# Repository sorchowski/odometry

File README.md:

# Odometry

A collection of classes, Arduino sketches, and hardware schematics to form a system for reading wheel rotational velocity.

# Table of Contents
1. [Components](#components)
   - [LS7366](#ls7366)
      - [How to Use](#how-to-use)
      - [Default Configuration](#default-configuration)
      - [Example Arduino Sketch](#example-arduino-sketch)
2. [Interfaces](#interfaces)
   - [SPI](#spi)
   - [I2C](#i2c)
3. [Hardware](#hardware)
   - [5 Volt Shield](#5-volt-shield)
      - [5v Arduino Pin Mappings](#5v-arduino-pin-mappings)
   - [3 Volt Shield](#3-volt-shield)
      - [3v Arduino Pin Mappings](#3v-arduino-pin-mappings)
   - [I2C Standalone](#i2c-standalone)
4. [Testing](#testing)
5. [Future Features](#future-features)

# Components

## LS7366

The [LS7366R](https://lsicsi.com/datasheets/LS7366R.pdf) is a 32-bit Quadrature Encoder chip interfaced via SPI. [This class](src/lib/Odometry/src/OdometryClass/ls7366) abstracts the various capabilities of the chip to a set of easily-invoked methods.

### How to Use

The QuadratureEncoder class resides within the LS7366R namespace.

1. Define the desired LS7366R flags.
2. Define a SPI chip select pin.
3. Instantiate the QuadratureEncoder class.
4. Call "init()" on this object.
5. Invoke "count()" and "status()" as desired.

### Default Configuration

Default values, MDR0_DEFAULT_CONFIG and MDR1_DEFAULT_CONFIG, are available for the MDR0 and MDR1 configuration registers.

See the [LS7366R.h header file](src/lib/Odometry/src/OdometryClass/ls7366/LS7366R.h) for a complete list of availavble options. These are 'OR-ed' together to obtain final register values.

### Example Arduino sketch

```
#include <LS7366R.h>
#include <SPI.h>

#define ENCODER_SS 10

using namespace LS7366R;

byte MDR0_CONFIG = MDR0_X1QUAD|MDR0_FREE_CNT|MDR0_IDX_DISABLE|MDR0_FILTR_CLK_DIV1;
byte MDR1_CONFIG = MDR1_CNT_4BYTE|MDR1_FLAG_NONE;

QuadratureEncoder encoder(ENCODER_SS, MDR0_CONFIG, MDR1_CONFIG);

void setup(){
  pinMode(ENCODER_SS, OUTPUT);
  SPI.begin();
  encoder.init();
}

void loop() {
  long count = encoder.count();
  byte status = encoder.status();
}
```

The full sketch is available under [LS7366-basic](src/lib/Odometry/examples/ArduinoSPI/LS7366-basic).

A sketch which manually executes raw SPI commands directly to chip to demonstrate the quadrature capabilities is also available under [LS7366-raw](src/lib/Odometry/examples/ArduinoSPI/LS7366-raw).

# Interfaces

[Odometry.h](src/lib/Odometry/src/Odometry.h) declares basic velocity and directional methods common to either SPI or I2C implementations.

TODO: describe defining wheel measurements and action of class to obtain velocity in meters/s

## SPI

[ArduinoOdometrySPI](src/lib/Odometry/src/OdometryClass/spi) - Provides an implementation of AbstractOdometry for connecting an Arduino to an Ls7366R quadrature encoder via the SPI interface.

## I2C

[ArduinoI2COdometry](src/lib/Odometry/src/OdometryClass/i2chost) - Provides an implementation of AnstractOdometry for connecting an Arduino to a peripheral over the I2C interface. The peripheral implements the interface to the LS7366 chip. See the [ArduinoI2CPeripheral.ino](src/lib/Odometry/examples/ArduinoI2C/ArduinoI2CPeripheral/ArduinoI2CPeripheral.ino) sketch for the example implementation.

[OdometryPayload.h](src/lib/Odometry/src/OdometryClass/OdometryPayload.h) provides a struct definition for packaging quadrature encoder count and status data to be transmitted over the I2C line.

# Hardware

Several Arduino shields are available. Each shield contains two LS7366 Quadrature Encoder chips for tracking encoder counts. Dual JST connectors for 3.3v and 5.0v power are available along with a pair of [I2C qwiic connectors](https://www.sparkfun.com/qwiic).

The LS7366 chip operates at 5 volts and the accompanying 40 Mhz oscillator also requires 5 volts as well.

Each shield is created using a free version of Autodesk EAGLE cad and fabricated using [Oshpark](https://oshpark.com/).

## 5 Volt Shield

The [5 volt shield](schematics/DualEncoderShield5v) is meant for use with an Arduino that operates I/O logic levels between 0 and 5 volts; such as an Uno.

The 5 volt shield exposes the DFLAG and LFLAG outputs of the LS7366 chip.

Onboard jumpers enable users to map the features below to any pin. But the pins listed below are the default when utilizing a simple two-pin jumper.

### 5v Arduino Pin Mappings

Encoder One (near the Dx pins)

Feature | Pin
--- | ---
Chip Select | 10
L1 | 7
D1 | 5

Encoder Two (near the Ax and power pins)

Feature | Pin
--- | ---
Chip Select | 9
L2 | 6
D2 | 4

## 3 Volt Shield

The [3.3 volt shield](schematics/DualEncoderShield3v) is meant for use with an Arduino that operates with I/O logic levels between 0 and 3.3 volts; such as a Due. A TXU0304 chip on board provides level-shifting for SPI and one chip select signal. A single TXU0101 translates the other chip select signal for the second encoder.

The 3.3 volt shield does not expose the DFLAG nor LFLAG outputs of the LS7366 chip.

Onboard jumpers enable users to map the features below to any pin. But the pins listed below are the default when utilizing a simple two-pin jumper.

### 3v Arduino Pin Mappings

Encoder One (near the Dx pins)
Feature | Pin
--- | ---
Chip Select | 9

Encoder Two (near the Ax and power pins)
Feature | Pin
--- | ---
Chip Select | 10

## I2C Standalone

A standalone peripheral board is available for use with an I2C interface. This board contains its own Atmega328 mcu and exposes both a 5v and 3.3v I2C interface to any host controller.

A PCA9306D chip provides logic level translation between 5v and 3.3v for the I2C interface.

Of course, either the 3.3v or 5v shields can also be used as a I2C peripheral when attached to an Arduino with the appropriate peripheral sketch uploaded.

Note, the latest revision of the I2C standalone board is not tested nor confirmed to work properly.

# Testing

## Velocity

To test the velocity measurements, a small, simple, two-wheeled cart ran in a straight line over measured intervals each of one meter. Note, the cart starting point was slightly before the first one meter marker. This is to allow the cart to reach a full and consistent speed before timing is begun.

See [image of the test setup](docs/testing/testing-vehicle-odometry.jpg)

Video of the test is [here](https://youtube.com/shorts/Ld17I0CanR0)

### Radians per second

In testing radiansPerSecond(), I observed 10 revolutions over 15.88 seconds. The measured value returned by this method was roughly 3.98 radians per second.

Using a visual method of measuring the rotation of the wheel with a tape mark and a timer; we can count 10 revolutions of the tape marker while timing how long these revolutions took.

There are 2*pi radians in a revolution = 6.283. 10 revolutions times 6.283 radians per revolution = 62.83 radians over 15.88 seconds. 62.83 radians / 15.88 seconds = 3.956 radians per second; which is close to the value output by the odometry logic.

Note, the visual method of measuring wheel rotations and timing each one is subject to human inaccuracies :)

Video of the test is [here](https://youtube.com/shorts/RxdmSXZlh9c)

# Future Features

* Implement the DFLAG and LFLAG signals for the 3.3v shield via use of four additional TXU0101 chips.
* Create an abstract SPI class and then Arduino-specific SPI class implementation. Modify the LS7366 class to accept an abstract SPI "interface" class to make the LS7366 class independent of an specific host and generic to any SPI interface.
* Create an abstract Quadrature class and pass an instance of this to the Odometry class. This makes the Odometry class independent of how quadrature counts are obtained. Convert the existing QuadratureEncoder class to a LS7366-specific implementation class.
* Rename "getVelocity()" to just "velocity()".
* See note in ArduinoSPIOdometry.h. Both getVelocity() and radiansPerSecond() invoke getCounts(). Therefore, callers of these methods have to be careful when passing the time delta value to either if both are present in a program. We should extract the call to getCounts() to a public method named "update()" which syncs the current count values. Subsequent calls to either getVelocity() or radiansPerSecond() are passed the time delta of the last two calls of "update()" and simply calculate the odometry measurements based on the last updated count values.
* Update the 3.3 volt shield to expose the DFLAG and LFLAG outputs of the 5v LS7366 chip.

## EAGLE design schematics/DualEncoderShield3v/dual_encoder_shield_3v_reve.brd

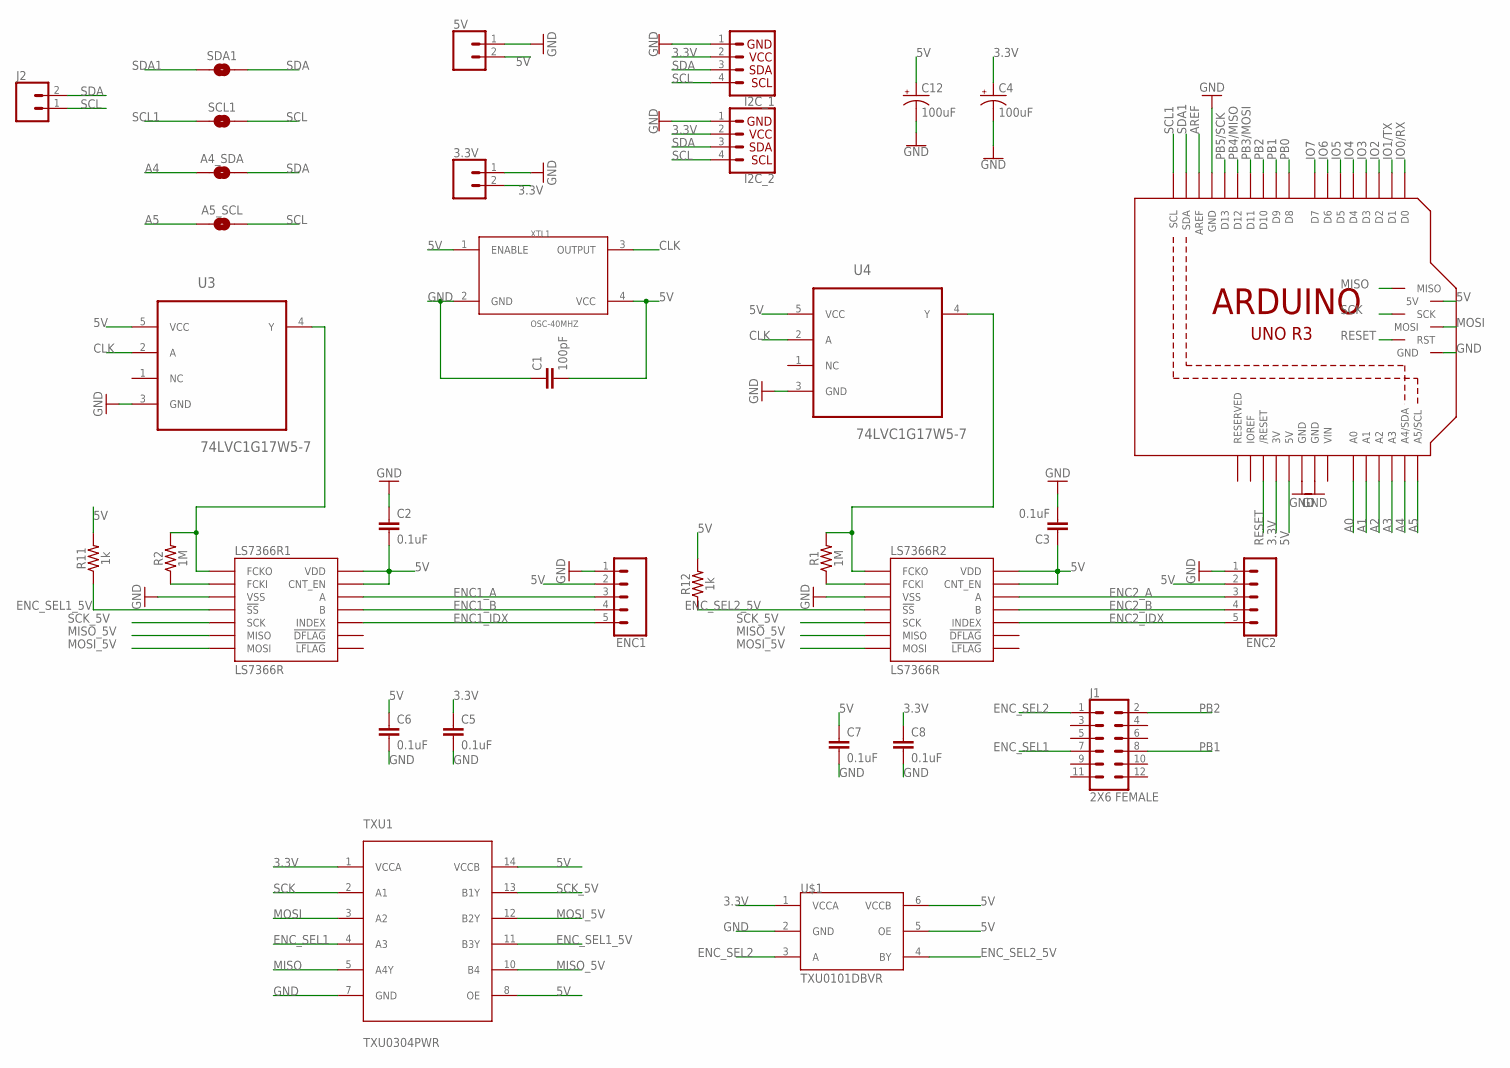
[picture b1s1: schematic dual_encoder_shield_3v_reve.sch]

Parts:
3.3V, 5V: CONN_02-JST-2MM-SMT; JST-2-SMD
A4_SDA, A5_SCL: JUMPER-SMT_2_NO_NO-SILK; SMT-JUMPER_2_NO_NO-SILK
C1: 100pF; 0603
C2, C3, C5, C6, C7, C8: 0.1uF; 0603
C4, C12: 100uF; PANASONIC_D
ENC1, ENC2: CONN_05; 1X05
I2C_1, I2C_2: QWIIC_CONNECTORJS-1MM; JST04_1MM_RA
J1: 2X6 FEMALE; 2X6
J2: CONN_02; 1X02
LS7366R1, LS7366R2: LS7366R; SOIC14
M1: ARDUINO_R3_ICSP; ARDUINOR3_ICSP
R1, R2: 1M; 0603
R11, R12: 1k; 0603
SCL1: JUMPER-SMT_2_NO_NO-SILK; SMT-JUMPER_2_NO_NO-SILK
SDA1: JUMPER-SMT_2_NO_NO-SILK; SMT-JUMPER_2_NO_NO-SILK
TXU1: TXU0304PWR; SOP65P640X95-14N
U3, U4: 74LVC1G17W5-7; SOT95P280X145-5N
U$1: TXU0101DBVR; SOT23-6
XTL1: OSC-40MHZ; OSC_CB3LV-5I-50M000000

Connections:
3.3V: 3.3V.2 (1), C4.+, C5.1, C8.1, I2C_1.2, I2C_2.2, M1.3V, TXU1.1 (VCCA), U$1.1 (VCCA)
5V: 5V.2 (1), C1.2, C2.2, C3.1, C6.1, C7.1, C12.+, ENC1.2, ENC2.2, LS7366R1.13 (CNT_EN), LS7366R1.14 (VDD), LS7366R2.13 (CNT_EN), LS7366R2.14 (VDD), M1.5V, M1.5V_ICSP (5V), R11.2, R12.2, TXU1.8 (OE), TXU1.14 (VCCB), U3.5 (VCC), U4.5 (VCC), U$1.5 (OE), U$1.6 (VCCB), XTL1.1 (ENABLE), XTL1.4 (VCC)
A0: M1.A0
A1: M1.A1
A2: M1.A2
A3: M1.A3
A4: A4_SDA.1, M1.A4 (A4/SDA)
A5: A5_SCL.1, M1.A5 (A5/SCL)
AREF: M1.AREF
CLK: U3.2 (A), U4.2 (A), XTL1.3 (OUTPUT)
ENC1_A: ENC1.3, LS7366R1.12 (A)
ENC1_B: ENC1.4, LS7366R1.11 (B)
ENC1_IDX: ENC1.5, LS7366R1.10 (INDEX)
ENC2_A: ENC2.3, LS7366R2.12 (A)
ENC2_B: ENC2.4, LS7366R2.11 (B)
ENC2_IDX: ENC2.5, LS7366R2.10 (INDEX)
ENC_SEL1: J1.7, TXU1.4 (A3)
ENC_SEL1_5V: LS7366R1.4 (!SS), R11.1, TXU1.11 (B3Y)
ENC_SEL2: J1.1, U$1.3 (A)
ENC_SEL2_5V: LS7366R2.4 (!SS), R12.1, U$1.4 (BY)
GND: 3.3V.1 (2), 5V.1 (2), C1.1, C2.1, C3.2, C4.-, C5.2, C6.2, C7.2, C8.2, C12.-, ENC1.1, ENC2.1, I2C_1.1, I2C_2.1, LS7366R1.3 (VSS), LS7366R2.3 (VSS), M1.GND, M1.GND@1 (GND), M1.GND@2 (GND), M1.GND@3 (GND), TXU1.7 (GND), U3.3 (GND), U4.3 (GND), U$1.2 (GND), XTL1.2 (GND)
IO0/RX: M1.D0
IO1/TX: M1.D1
IO2: M1.D2
IO3: M1.D3
IO4: M1.D4
IO5: M1.D5
IO6: M1.D6
IO7: M1.D7
MISO: M1.MISO, TXU1.5 (A4Y)
MISO_5V: LS7366R1.6 (MISO), LS7366R2.6 (MISO), TXU1.10 (B4)
MOSI: M1.MOSI, TXU1.3 (A2)
MOSI_5V: LS7366R1.7 (MOSI), LS7366R2.7 (MOSI), TXU1.12 (B2Y)
unnamed: LS7366R1.2 (FCKI), R2.1
unnamed: LS7366R2.1 (FCKO), R1.2, U4.4 (Y)
unnamed: LS7366R2.2 (FCKI), R1.1
unnamed: LS7366R1.1 (FCKO), R2.2, U3.4 (Y)
PB0: M1.D8
PB1: J1.8, M1.D9
PB2: J1.2, M1.D10
PB3/MOSI: M1.D11
PB4/MISO: M1.D12
PB5/SCK: M1.D13
RESET: M1.RESET (/RESET), M1.RESET_ICSP (RST)
SCK: M1.SCK, TXU1.2 (A1)
SCK_5V: LS7366R1.5 (SCK), LS7366R2.5 (SCK), TXU1.13 (B1Y)
SCL: A5_SCL.2, I2C_1.4, I2C_2.4, J2.1, SCL1.2
SCL1: M1.SCL, SCL1.1
SDA: A4_SDA.2, I2C_1.3, I2C_2.3, J2.2, SDA1.2
SDA1: M1.SDA, SDA1.1
VIN: M1.VIN

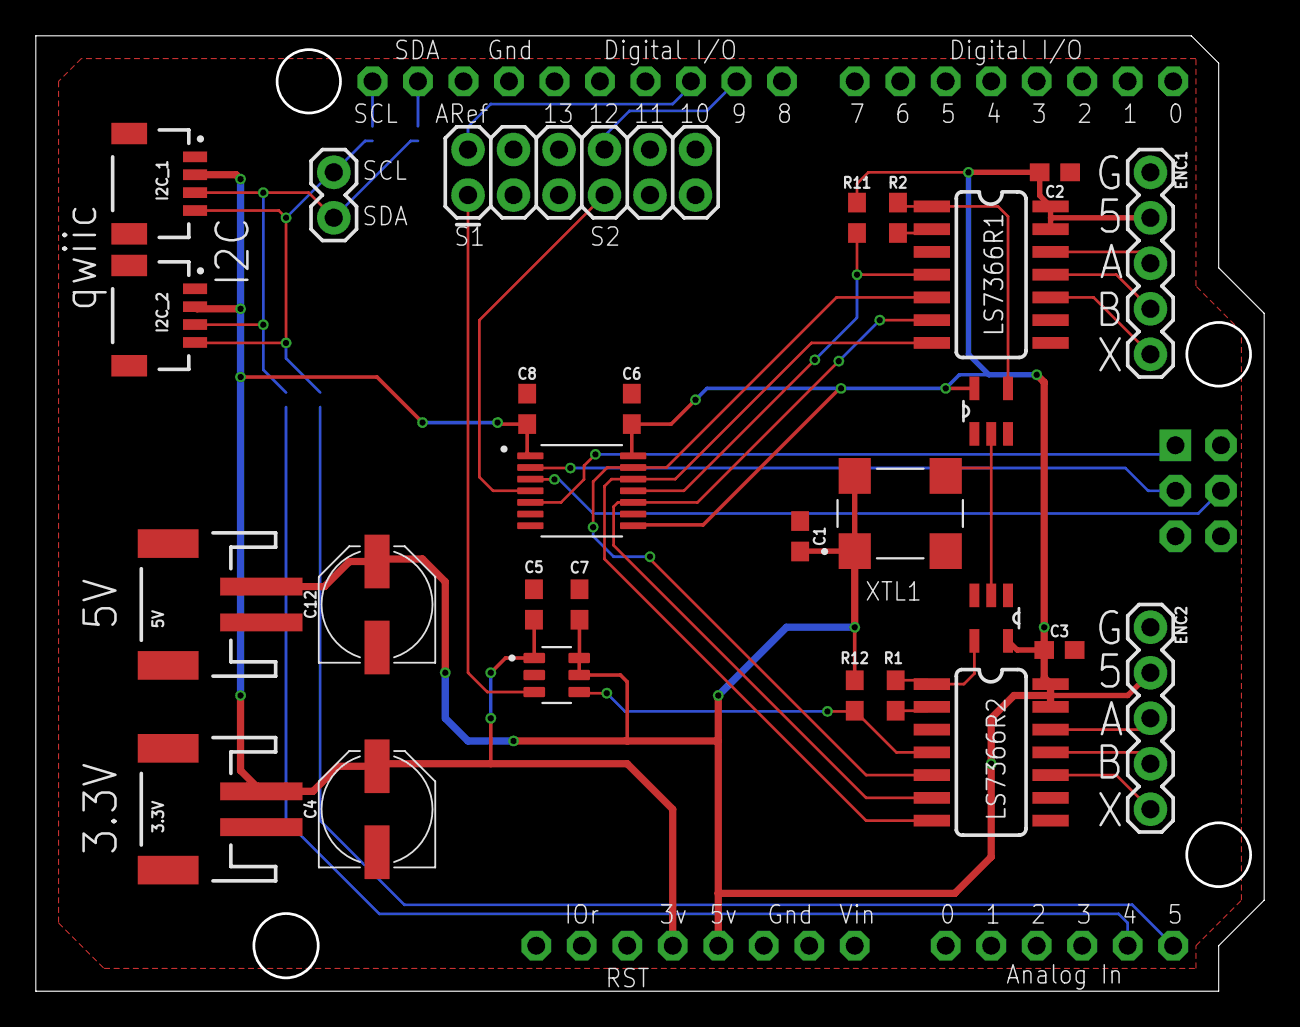
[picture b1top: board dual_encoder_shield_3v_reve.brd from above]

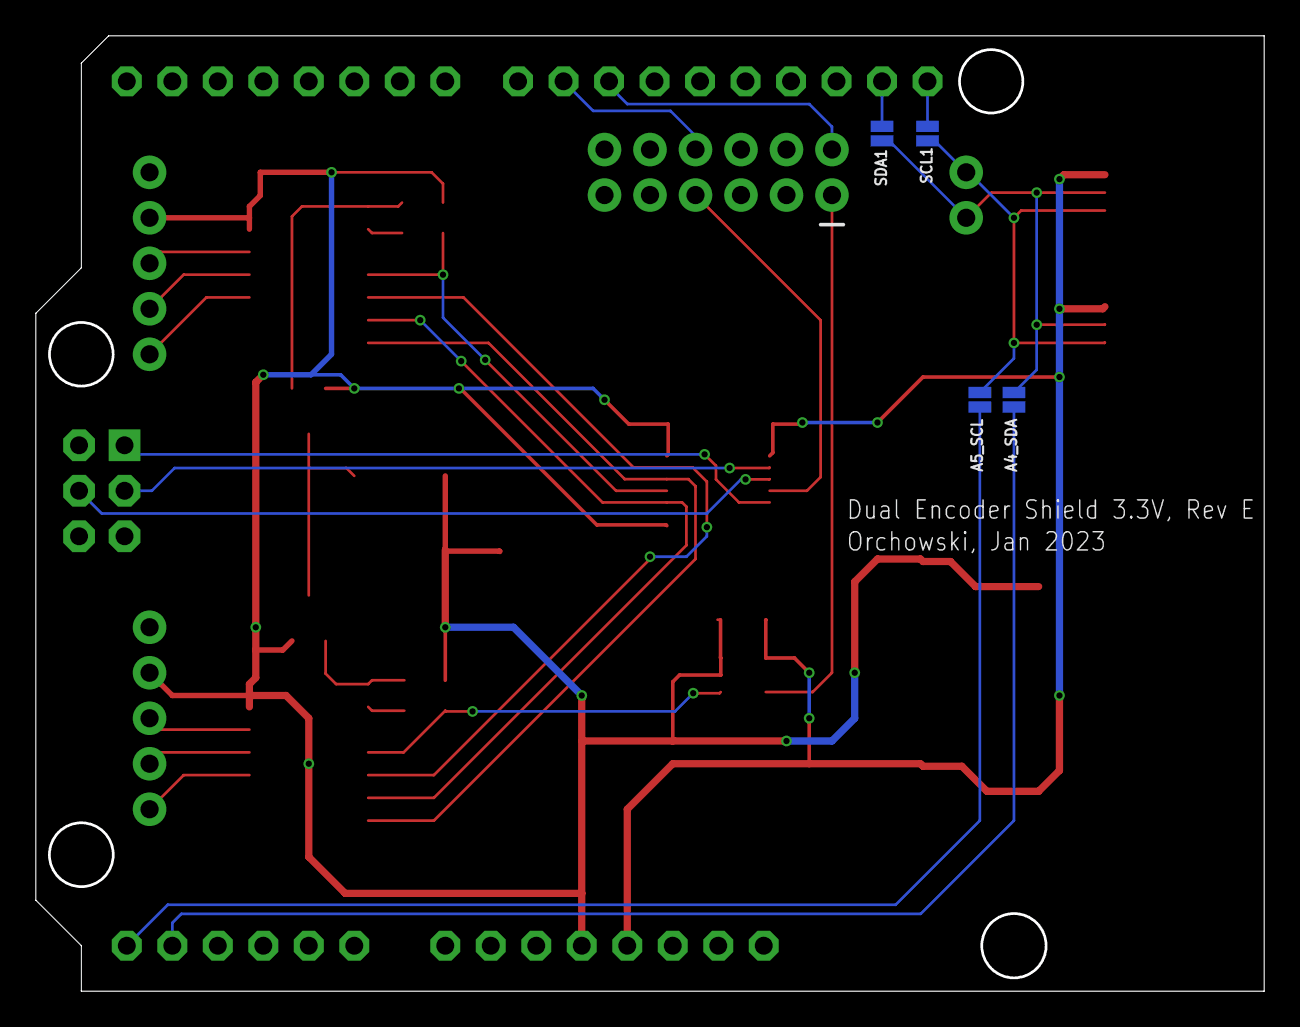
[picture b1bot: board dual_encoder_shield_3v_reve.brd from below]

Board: 2 copper layers, 68.4 x 53.2 mm, 33 parts (4 on the bottom side), 33 nets.

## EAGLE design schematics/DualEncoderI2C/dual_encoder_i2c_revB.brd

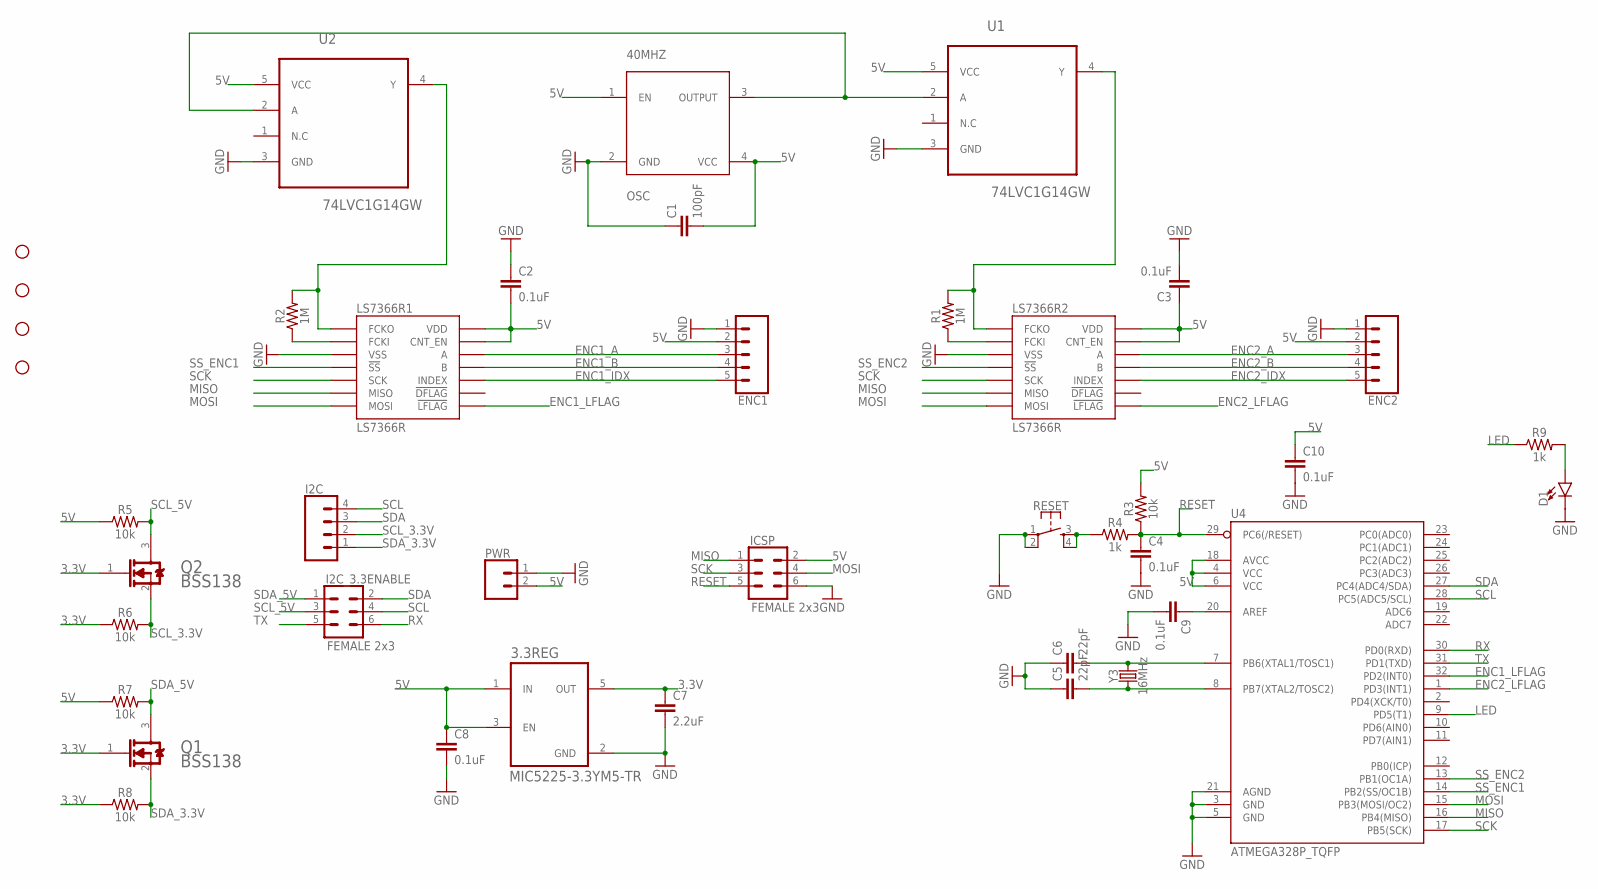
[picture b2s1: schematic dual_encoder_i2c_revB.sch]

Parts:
3.3REG: MIC5225-3.3YM5-TR; SOT95P280X145-5N
40MHZ: OSC; CB3OSCILLATOR
C1: 100pF; 0603
C2, C3, C4, C8, C9, C10: 0.1uF; 0603
C5, C6: 22pF; 0603
C7: 2.2uF; 0603
D1: LED0603; LED-0603
ENC1, ENC2: CONN_05; 1X05
H1, H2, H3, H4: STAND-OFF
I2C: CONN_04; 1X04
I2C_3.3ENABLE: FEMALE 2x3; 2X3
ICSP: FEMALE 2x3; 2X3
LS7366R1, LS7366R2: LS7366R; SOIC14
PWR: CONN_02-JST-2MM-SMT; JST-2-SMD
Q1, Q2: ON_SEMI_BSS138ON_SEMI_BSS138_0_0; ON_SEMI_BSS138_0
R1, R2: 1M; 0603
R3, R5, R6, R7, R8: 10k; 0603
R4, R9: 1k; 0603
RESET: MOMENTARY-SWITCH-SPST-2-SMD-5.2MM; TACTILE_SWITCH_SMD_5.2MM
U1, U2: 74LVC1G14GW; SOT65P210X110-5N
U4: ATMEGA328P_TQFP; TQFP32-08
Y3: 16MHz; CRYSTAL-SMD-5X3.2-4PAD

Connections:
3.3V: 3.3REG.5 (OUT), C7.1, Q1.1 (G), Q2.1 (G), R6.1, R8.1
5V: 3.3REG.1 (IN), 3.3REG.3 (EN), 40MHZ.1 (EN), 40MHZ.4 (VCC), C1.2, C2.2, C3.1, C8.1, C10.1, ENC1.2, ENC2.2, ICSP.2, LS7366R1.13 (CNT_EN), LS7366R1.14 (VDD), LS7366R2.13 (CNT_EN), LS7366R2.14 (VDD), PWR.2 (1), R3.2, R5.1, R7.1, U1.5 (VCC), U2.5 (VCC), U4.4 (VCC), U4.6 (VCC), U4.18 (AVCC)
ENC1_A: ENC1.3, LS7366R1.12 (A)
ENC1_B: ENC1.4, LS7366R1.11 (B)
ENC1_IDX: ENC1.5, LS7366R1.10 (INDEX)
ENC1_LFLAG: LS7366R1.8 (!LFLAG), U4.32 (PD2(INT0))
ENC2_A: ENC2.3, LS7366R2.12 (A)
ENC2_B: ENC2.4, LS7366R2.11 (B)
ENC2_IDX: ENC2.5, LS7366R2.10 (INDEX)
ENC2_LFLAG: LS7366R2.8 (!LFLAG), U4.1 (PD3(INT1))
GND: 3.3REG.2 (GND), 40MHZ.2 (GND), C1.1, C2.1, C3.2, C4.2, C5.1, C6.1, C7.2, C8.2, C9.2, C10.2, D1.C, ENC1.1, ENC2.1, ICSP.6, LS7366R1.3 (VSS), LS7366R2.3 (VSS), PWR.1 (2), RESET.1, RESET.2, U1.3 (GND), U2.3 (GND), U4.3 (GND), U4.5 (GND), U4.21 (AGND)
LED: R9.1, U4.9 (PD5(T1))
MISO: ICSP.1, LS7366R1.6 (MISO), LS7366R2.6 (MISO), U4.16 (PB4(MISO))
MOSI: ICSP.4, LS7366R1.7 (MOSI), LS7366R2.7 (MOSI), U4.15 (PB3(MOSI/OC2))
unnamed: C9.1, U4.20 (AREF)
unnamed: R4.1, RESET.3, RESET.4
unnamed: D1.A, R9.2
unnamed: LS7366R1.2 (FCKI), R2.1
unnamed: 40MHZ.3 (OUTPUT), U1.2 (A), U2.2 (A)
unnamed: LS7366R2.1 (FCKO), R1.2, U1.4 (Y)
unnamed: LS7366R2.2 (FCKI), R1.1
unnamed: LS7366R1.1 (FCKO), R2.2, U2.4 (Y)
unnamed: C6.2, U4.7 (PB6(XTAL1/TOSC1)), Y3.3 (2)
unnamed: C5.2, U4.8 (PB7(XTAL2/TOSC2)), Y3.1
RESET: C4.1, ICSP.5, R3.1, R4.2, U4.29 (PC6(/RESET))
RX: I2C_3.3ENABLE.6, U4.30 (PD0(RXD))
SCK: ICSP.3, LS7366R1.5 (SCK), LS7366R2.5 (SCK), U4.17 (PB5(SCK))
SCL: I2C.4, I2C_3.3ENABLE.4, U4.28 (PC5(ADC5/SCL))
SCL_3.3V: I2C.2, Q2.2 (S), R6.2
SCL_5V: I2C_3.3ENABLE.3, Q2.3 (D), R5.2
SDA: I2C.3, I2C_3.3ENABLE.2, U4.27 (PC4(ADC4/SDA))
SDA_3.3V: I2C.1, Q1.2 (S), R8.2
SDA_5V: I2C_3.3ENABLE.1, Q1.3 (D), R7.2
SS_ENC1: LS7366R1.4 (!SS), U4.14 (PB2(SS/OC1B))
SS_ENC2: LS7366R2.4 (!SS), U4.13 (PB1(OC1A))
TX: I2C_3.3ENABLE.5, U4.31 (PD1(TXD))

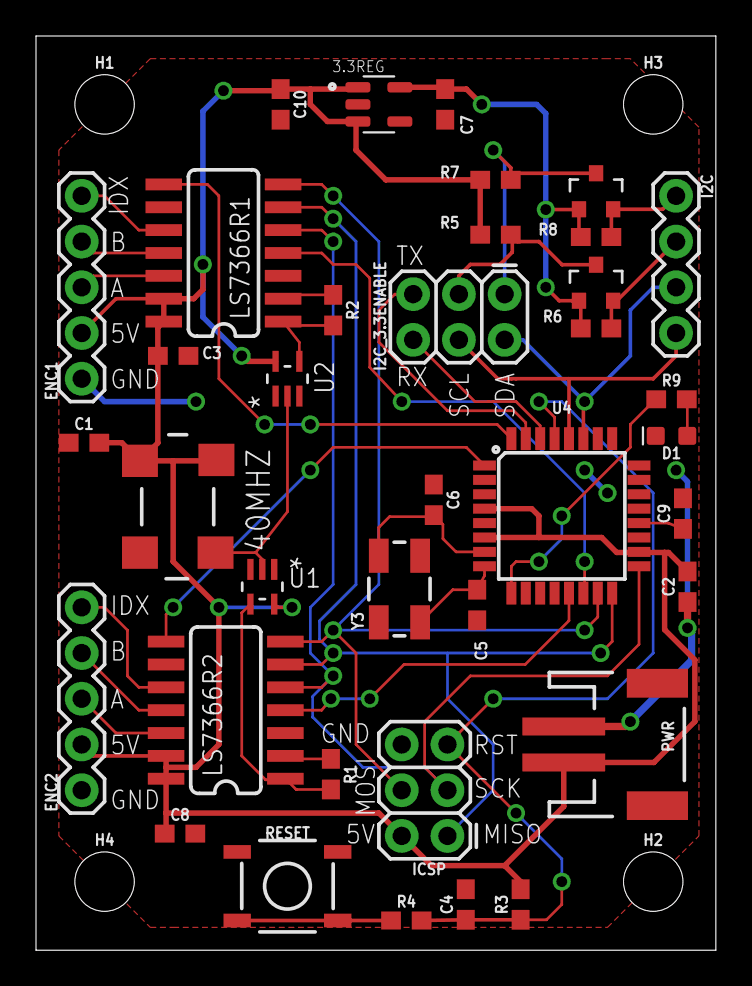
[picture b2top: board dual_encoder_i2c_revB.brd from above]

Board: 2 copper layers, 37.8 x 50.8 mm, 41 parts (0 on the bottom side), 36 nets.

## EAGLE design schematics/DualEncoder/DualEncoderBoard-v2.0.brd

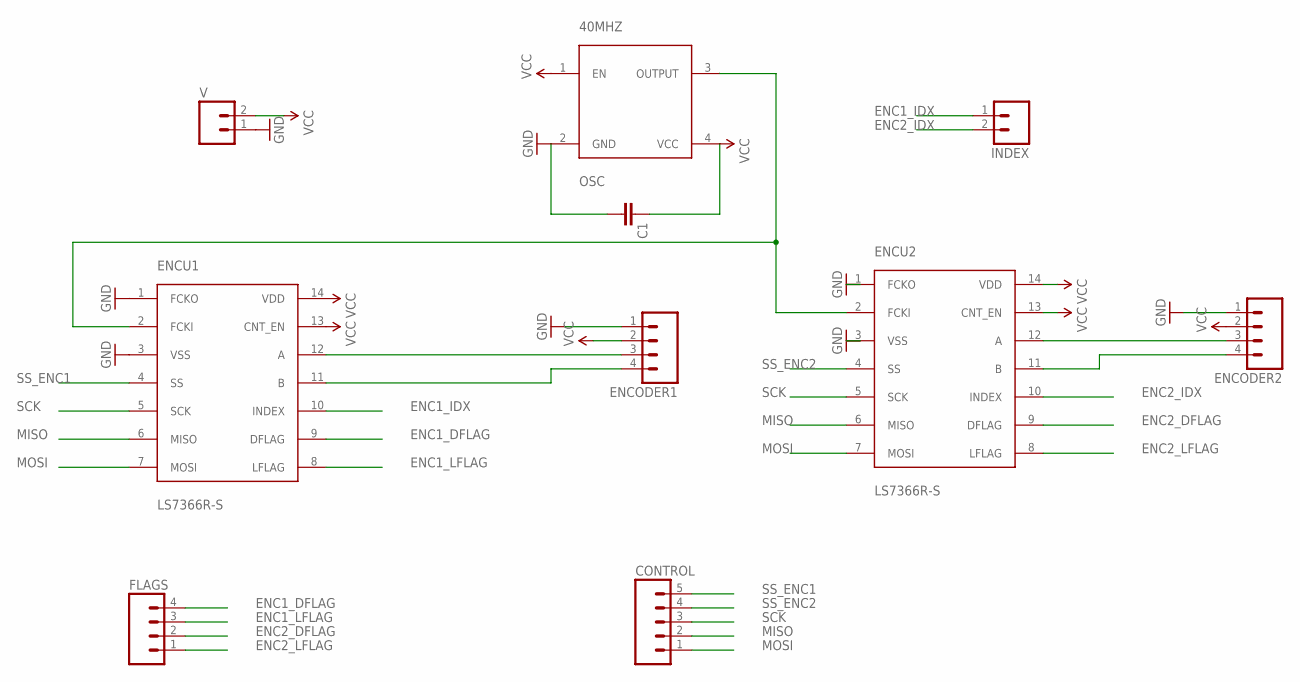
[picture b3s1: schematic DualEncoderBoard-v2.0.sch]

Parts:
40MHZ: OSC; CB3OSCILLATOR
C1: CAPKIT; CAP-PTH-SMALL-KIT
CONTROL: M05PTH; 1X05
ENCODER1, ENCODER2: M04POLAR; MOLEX-1X4
ENCU1, ENCU2: LS7366R-S; SO14
FLAGS: M04PTH; 1X04
INDEX: M02PTH; 1X02
V: M02-JST-2MM-SMT; JST-2-SMD

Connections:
ENC1_DFLAG: ENCU1.9 (DFLAG), FLAGS.4
ENC1_IDX: ENCU1.10 (INDEX), INDEX.1
ENC1_LFLAG: ENCU1.8 (LFLAG), FLAGS.3
ENC2_DFLAG: ENCU2.9 (DFLAG), FLAGS.2
ENC2_IDX: ENCU2.10 (INDEX), INDEX.2
ENC2_LFLAG: ENCU2.8 (LFLAG), FLAGS.1
GND: 40MHZ.2 (GND), C1.2, ENCODER1.1, ENCODER2.1, ENCU1.1 (FCKO), ENCU1.3 (VSS), ENCU2.1 (FCKO), ENCU2.3 (VSS), V.1
MISO: CONTROL.2, ENCU1.6 (MISO), ENCU2.6 (MISO)
MOSI: CONTROL.1, ENCU1.7 (MOSI), ENCU2.7 (MOSI)
unnamed: ENCODER1.3, ENCU1.12 (A)
unnamed: ENCODER1.4, ENCU1.11 (B)
unnamed: ENCODER2.3, ENCU2.12 (A)
unnamed: ENCODER2.4, ENCU2.11 (B)
unnamed: 40MHZ.3 (OUTPUT), ENCU1.2 (FCKI), ENCU2.2 (FCKI)
SCK: CONTROL.3, ENCU1.5 (SCK), ENCU2.5 (SCK)
SS_ENC1: CONTROL.5, ENCU1.4 (SS)
SS_ENC2: CONTROL.4, ENCU2.4 (SS)
VCC: 40MHZ.1 (EN), 40MHZ.4 (VCC), C1.1, ENCODER1.2, ENCODER2.2, ENCU1.13 (CNT_EN), ENCU1.14 (VDD), ENCU2.13 (CNT_EN), ENCU2.14 (VDD), V.2

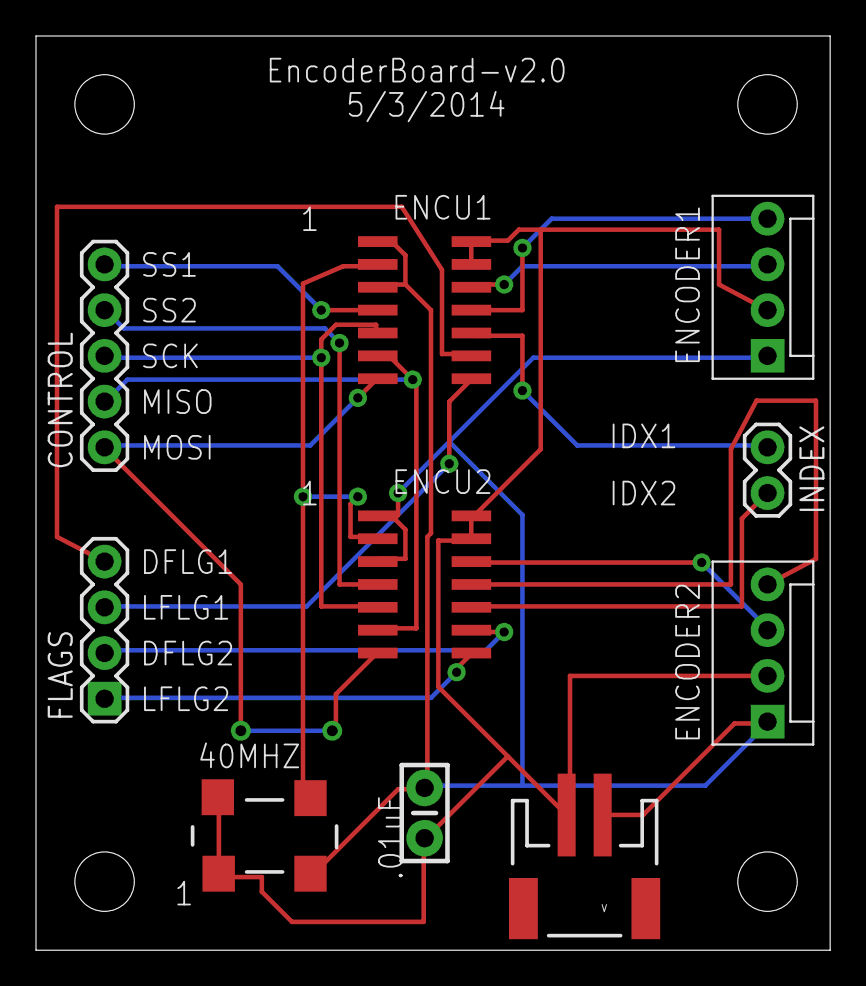
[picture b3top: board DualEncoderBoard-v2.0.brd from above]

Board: 2 copper layers, 44.1 x 50.8 mm, 14 parts (0 on the bottom side), 18 nets.

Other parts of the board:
U$1, U$2, U$3, U$4: STAND-OFF

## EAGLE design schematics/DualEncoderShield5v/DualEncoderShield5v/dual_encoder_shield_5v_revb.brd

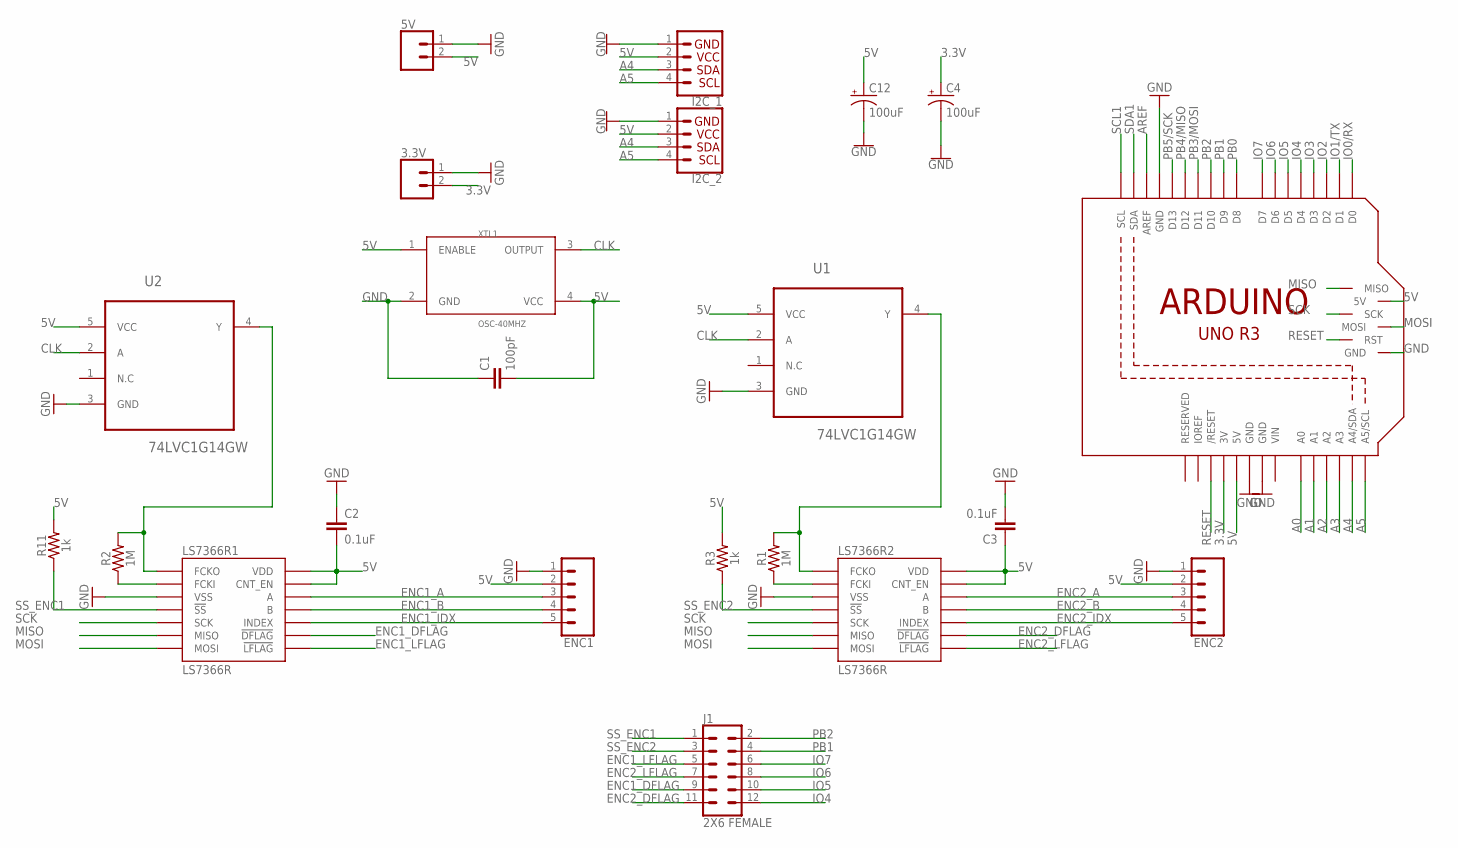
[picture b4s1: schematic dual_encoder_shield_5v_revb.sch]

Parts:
3.3V, 5V: CONN_02-JST-2MM-SMT; JST-2-SMD
C1: 100pF; 0603
C2, C3: 0.1uF; 0603
C4, C12: 100uF; PANASONIC_D
ENC1, ENC2: CONN_05; 1X05
I2C_1, I2C_2: QWIIC_CONNECTORJS-1MM; JST04_1MM_RA
J1: 2X6 FEMALE; 2X6
LS7366R1, LS7366R2: LS7366R; SOIC14
M1: ARDUINO_R3_ICSP; ARDUINOR3_ICSP
R1, R2: 1M; 0603
R3, R11: 1k; 0603
U1, U2: 74LVC1G14GW; SOT65P210X110-5N
XTL1: OSC-40MHZ; OSC_CB3LV-5I-50M000000

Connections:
3.3V: 3.3V.2 (1), C4.+, M1.3V
5V: 5V.2 (1), C1.2, C2.2, C3.1, C12.+, ENC1.2, ENC2.2, I2C_1.2, I2C_2.2, LS7366R1.13 (CNT_EN), LS7366R1.14 (VDD), LS7366R2.13 (CNT_EN), LS7366R2.14 (VDD), M1.5V, M1.5V_ICSP (5V), R3.2, R11.2, U1.5 (VCC), U2.5 (VCC), XTL1.1 (ENABLE), XTL1.4 (VCC)
A0: M1.A0
A1: M1.A1
A2: M1.A2
A3: M1.A3
A4: I2C_1.3, I2C_2.3, M1.A4 (A4/SDA)
A5: I2C_1.4, I2C_2.4, M1.A5 (A5/SCL)
AREF: M1.AREF
CLK: U1.2 (A), U2.2 (A), XTL1.3 (OUTPUT)
ENC1_A: ENC1.3, LS7366R1.12 (A)
ENC1_B: ENC1.4, LS7366R1.11 (B)
ENC1_DFLAG: J1.9, LS7366R1.9 (!DFLAG)
ENC1_IDX: ENC1.5, LS7366R1.10 (INDEX)
ENC1_LFLAG: J1.5, LS7366R1.8 (!LFLAG)
ENC2_A: ENC2.3, LS7366R2.12 (A)
ENC2_B: ENC2.4, LS7366R2.11 (B)
ENC2_DFLAG: J1.11, LS7366R2.9 (!DFLAG)
ENC2_IDX: ENC2.5, LS7366R2.10 (INDEX)
ENC2_LFLAG: J1.7, LS7366R2.8 (!LFLAG)
GND: 3.3V.1 (2), 5V.1 (2), C1.1, C2.1, C3.2, C4.-, C12.-, ENC1.1, ENC2.1, I2C_1.1, I2C_2.1, LS7366R1.3 (VSS), LS7366R2.3 (VSS), M1.GND, M1.GND@1 (GND), M1.GND@2 (GND), M1.GND@3 (GND), U1.3 (GND), U2.3 (GND), XTL1.2 (GND)
IO0/RX: M1.D0
IO1/TX: M1.D1
IO2: M1.D2
IO3: M1.D3
IO4: J1.12, M1.D4
IO5: J1.10, M1.D5
IO6: J1.8, M1.D6
IO7: J1.6, M1.D7
MISO: LS7366R1.6 (MISO), LS7366R2.6 (MISO), M1.MISO
MOSI: LS7366R1.7 (MOSI), LS7366R2.7 (MOSI), M1.MOSI
unnamed: LS7366R1.2 (FCKI), R2.1
unnamed: LS7366R2.1 (FCKO), R1.2, U1.4 (Y)
unnamed: LS7366R2.2 (FCKI), R1.1
unnamed: LS7366R1.1 (FCKO), R2.2, U2.4 (Y)
PB0: M1.D8
PB1: J1.4, M1.D9
PB2: J1.2, M1.D10
PB3/MOSI: M1.D11
PB4/MISO: M1.D12
PB5/SCK: M1.D13
RESET: M1.RESET (/RESET), M1.RESET_ICSP (RST)
SCK: LS7366R1.5 (SCK), LS7366R2.5 (SCK), M1.SCK
SCL1: M1.SCL
SDA1: M1.SDA
SS_ENC1: J1.1, LS7366R1.4 (!SS), R11.1
SS_ENC2: J1.3, LS7366R2.4 (!SS), R3.1
VIN: M1.VIN

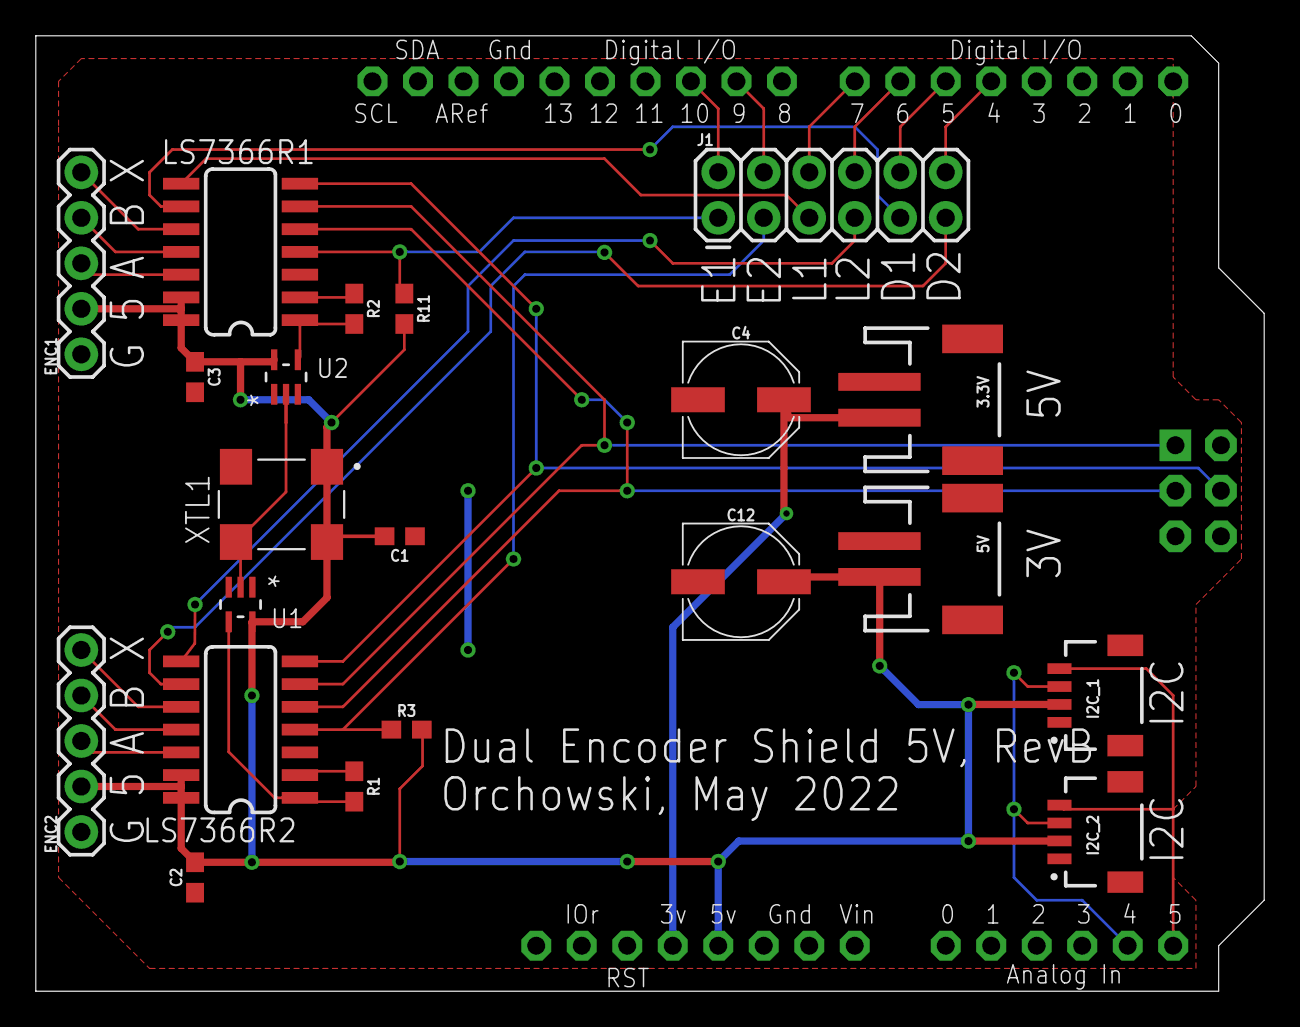
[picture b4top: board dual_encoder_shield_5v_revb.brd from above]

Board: 2 copper layers, 68.6 x 53.3 mm, 22 parts (0 on the bottom side), 32 nets.

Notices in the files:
parts and their libraries:
SparkFun: Licensing: CC v3.0 Share-Alike You are welcome to use this library for commercial purposes.
SparkFun-Capacitors: Licensing: Creative Commons ShareAlike 4.0 International - https://creativecommons.org/licenses/by-sa/4.0
